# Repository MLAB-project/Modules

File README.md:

# MLAB hardware modules main repository

The MLAB Project was created to develop an universal kit to support hobbyist and professionals in the construction of simple or more complicated devices and instruments (robots, automation systems, testing kits and so on). It is primarily intended for engineers and scientists and it is in continuous development since 2003.

**This repository is archived because its contents have been split into separate repositories in the [MLAB-modules](https://github.com/mlab-modules/) organization. The development of new [MLAB](https://www.mlab.cz) components is still in progress and development has not been suspended. You can read about the reasons of the repository split on the [Discussions thread](https://github.com/orgs/MLAB-project/discussions/1).**

This repository is only a component of the [complete MLAB system](http://www.mlab.cz/)

## Modules

The principle of [Modular LABoratory](http://www.mlab.cz) is based on decomposition of complex systems into smaller cells or bricks (in MLAB called [modules](http://wiki.mlab.cz/doku.php?id=en:moduly)) such as communication interfaces, operational amplifiers, CPU modules, FPGA programmers and many other. Over years of development, [tenths of modules have been created](https://github.com/mlab-modules) - for easier orientation they are sorted into categories which are the first-level folders of this repository. Many modules are included as [repository submodules](https://git-scm.com/book/en/v2/Git-Tools-Submodules) in this parent repository. 

When creating modules, great emphasis is put on the quality of design and construction. The results can, therefore, meet the standards of even the most demanding users from the community of researchers, experimenters and innovators.

## How to start using MLAB

Further information can be found on [MLAB Wiki](http://wiki.mlab.cz/).

There is also a [Mailing list](https://groups.google.com/forum/#!forum/mlab-users) available for users and developers.

## Compatibility

Thanks to careful design, most of the modules are dimensionally and electrically compatible with many other products. Examples include the Arduino platform, the Merkur construction set, optical tables and DIN switchboard systems.

## Applications

See the [list of designs](http://home.mlab.cz/Server/GenIndex/GenIndex.php?path=%2FDesigns&lang=en) for an illustration of the wide spectrum of possible applications.

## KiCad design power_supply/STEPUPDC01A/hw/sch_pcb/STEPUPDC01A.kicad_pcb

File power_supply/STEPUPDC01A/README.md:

<!--- PrjInfo ---> <!--- Please remove this line after manually editing --->
<!--- 00a56be08b96043df9e37d6aff7b6990 --->
<!--- Created:: --->
<!--- Author:: --->
<!--- AuthorEmail:: --->
<!--- Tags:: --->
<!--- Ust:: --->
<!--- Label --->
<!--- ELabel --->
<!--- Name:STEPUPDC01A: --->
# STEPUPDC01A
<!--- LongName --->
Step-Up DC/DC
<!--- ELongName --->

<!--- Lead --->
Vin 3 V - 11 V, Vout up to 36 V, maximal output power 120mW
<!--- ELead --->

<!--- Description --->
<!--- EDescription --->
<!--- Content --->
<!--- EContent --->

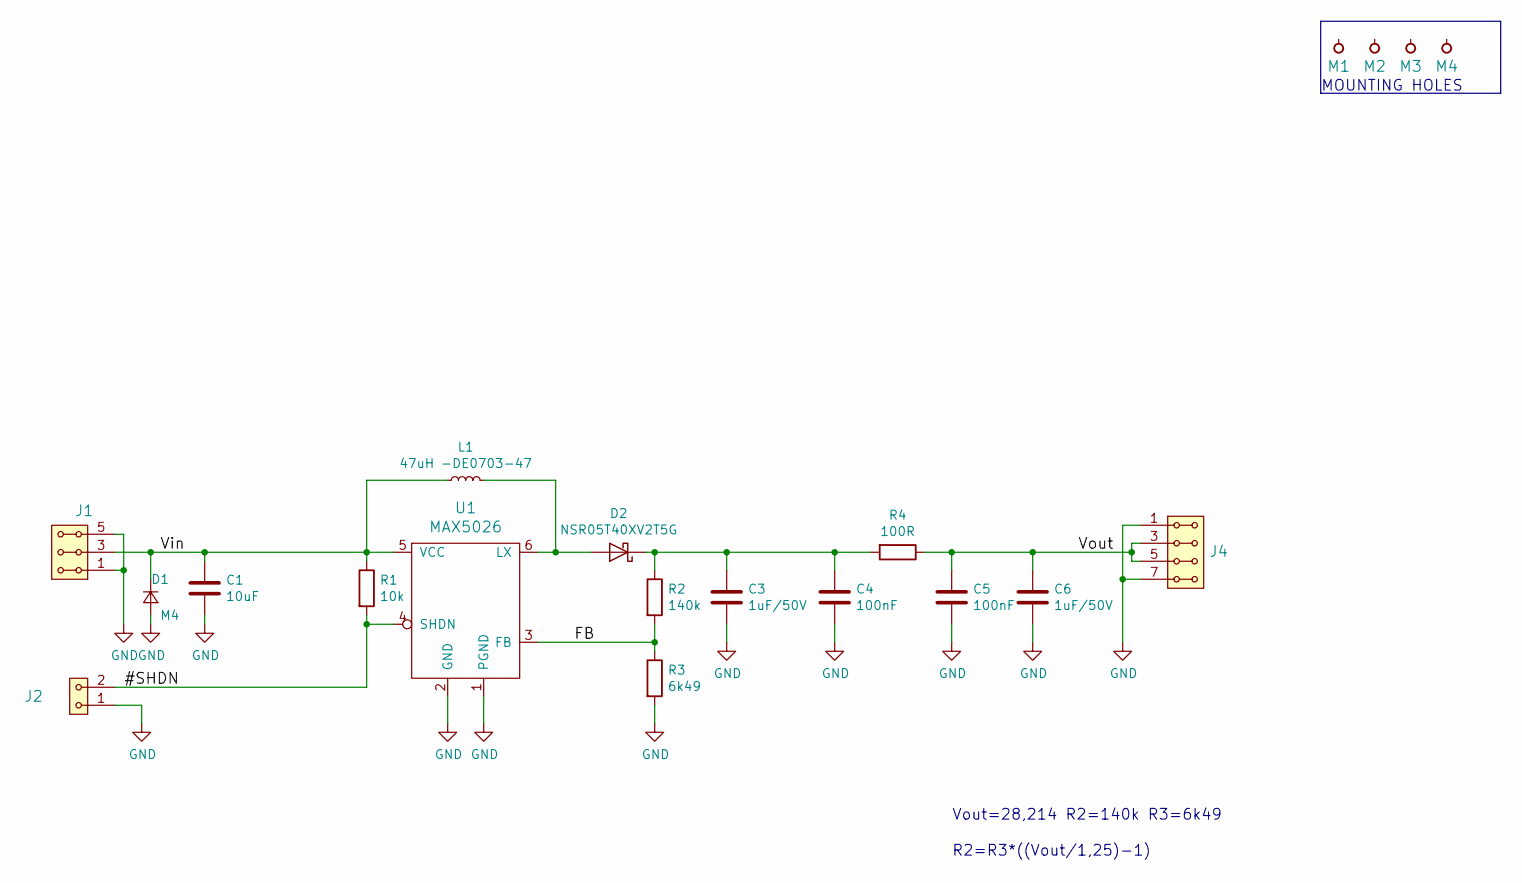
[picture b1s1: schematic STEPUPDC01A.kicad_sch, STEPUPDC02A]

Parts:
C1: 10uF; SMD-0805
C3, C6: 1uF/50V; SMD-0805
C4, C5: 100nF; SMD-0805
D1: M4; Diode-SMA_Standard
D2: NSR05T40XV2T5G; D_SOD-523
J1: HEADER_2x03_PARALLEL; Straight_2x03
J2: HEADER_1x02; Straight_1x02
J4: HEADER_2x04_PARALLEL; Straight_2x04
L1: 47uH -DE0703-47; DE0703
M1, M2, M3, M4: HOLE; MountingHole_3mm
R1: 10k; SMD-0805
R2: 140k; SMD-0805
R3: 6k49; SMD-0805
R4: 100R; SMD-0805
U1: MAX5026; SOT-23-6_Handsoldering

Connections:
/#SHDN: J2.2, R1.2, U1.4 (SHDN)
/FB: R2.2, R3.1, U1.3 (FB)
/Vin: C1.1, D1.1 (K), J1.3, J1.4, L1.1, R1.1, U1.5 (VCC)
/Vout: C5.1, C6.1, J4.3, J4.4, J4.5, J4.6, R4.1
GND: C1.2, C3.2, C4.2, C5.2, C6.2, D1.2 (A), J1.1, J1.2, J1.5, J1.6, J2.1, J4.1, J4.2, J4.7, J4.8, R3.2, U1.1 (PGND), U1.2 (GND)
unnamed: C3.1, C4.1, D2.1 (K), R2.1, R4.2
unnamed: D2.2 (A), L1.2, U1.6 (LX)

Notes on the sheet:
R2=R3*((Vout/1,25)-1)
Vout=28,214 R2=140k R3=6k49
MOUNTING HOLES

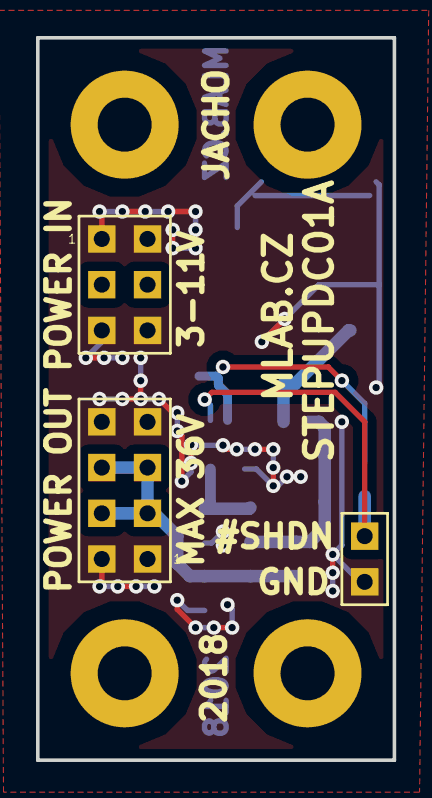
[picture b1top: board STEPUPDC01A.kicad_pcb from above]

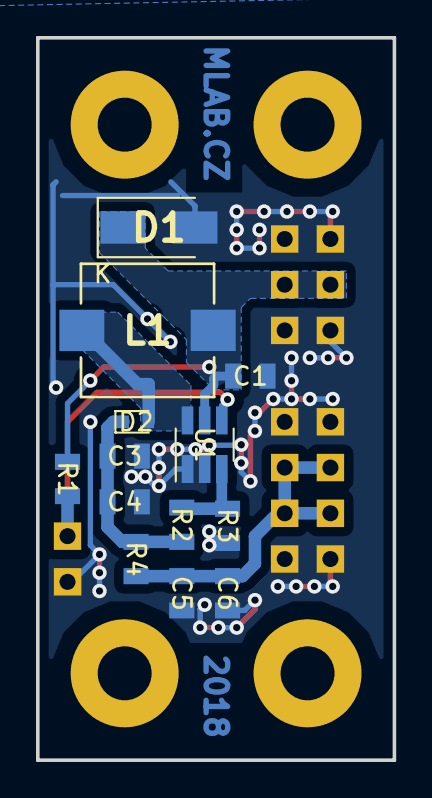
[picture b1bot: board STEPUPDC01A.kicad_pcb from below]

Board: 2 copper layers, 19.8 x 40.1 mm, 20 parts (13 on the bottom side), 7 nets.

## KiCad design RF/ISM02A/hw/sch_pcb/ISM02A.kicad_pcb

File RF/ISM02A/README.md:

<!--- PrjInfo ---> <!--- Please remove this line after manually editing --->
<!--- 00a56be08b96043df9e37d6aff7b6990 --->
<!--- Created:2022-02-16 22:22:32.926193: ---> 
<!--- Author:: ---> 
<!--- AuthorEmail:: ---> 
<!--- Tags:: ---> 
<!--- Ust:: ---> 
<!--- Label --->
<!--- ELabel ---> 
<!--- Name:ISM02A: --->
# ISM02A
<!--- LongName --->
## 
<!--- ELongName ---> 

<!--- Lead --->

<!--- ELead ---> 

<!--- Description --->
<!--- EDescription --->
<!--- Content --->
<!--- EContent --->
<sub><sup> Generated with [MLABweb](https://github.com/MLAB-project/MLABweb). (2022-02-16)</sup></sub>

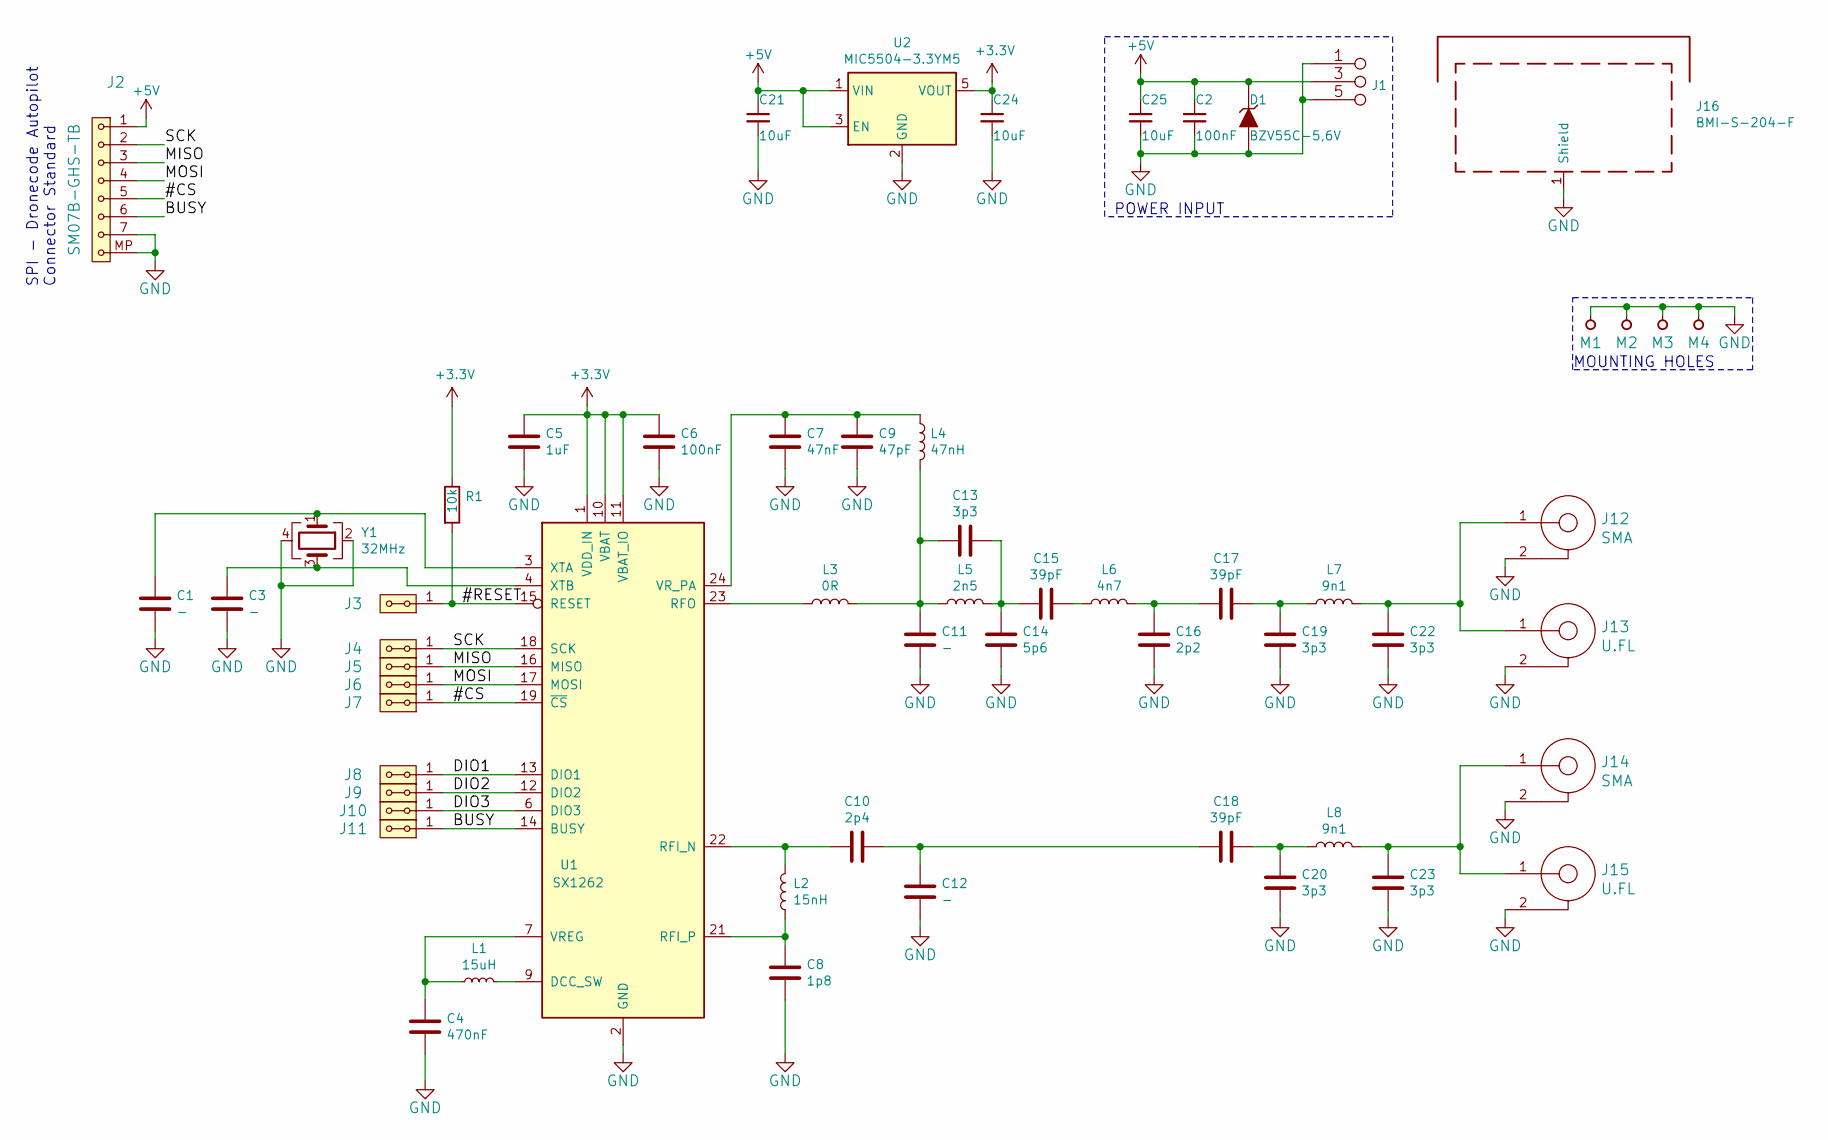
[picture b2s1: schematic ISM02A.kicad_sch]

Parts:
C1, C3, C11, C12: -; C_0603_1608Metric_Pad1.05x0.95mm_HandSolder
C2, C6: 100nF; C_0603_1608Metric_Pad1.05x0.95mm_HandSolder
C4: 470nF; C_0603_1608Metric_Pad1.05x0.95mm_HandSolder
C5: 1uF; C_0603_1608Metric_Pad1.05x0.95mm_HandSolder
C7: 47nF; C_0603_1608Metric_Pad1.05x0.95mm_HandSolder
C8: 1p8; C_0603_1608Metric_Pad1.05x0.95mm_HandSolder
C9: 47pF; C_0603_1608Metric_Pad1.05x0.95mm_HandSolder
C10: 2p4; C_0603_1608Metric_Pad1.05x0.95mm_HandSolder
C13, C19, C20, C22, C23: 3p3; C_0603_1608Metric_Pad1.05x0.95mm_HandSolder
C14: 5p6; C_0603_1608Metric_Pad1.05x0.95mm_HandSolder
C15, C17, C18: 39pF; C_0603_1608Metric_Pad1.05x0.95mm_HandSolder
C16: 2p2; C_0603_1608Metric_Pad1.05x0.95mm_HandSolder
C21, C24, C25: 10uF; SMD-0805
D1: BZV55C-5,6V; Diode-MiniMELF_Standard
J1: JUMP_3X2; Straight_2x03
J2: SM07B-GHS-TB; JST_GH_SM07B-GHS-TB_1x07-1MP_P1.25mm_Horizontal
J3, J4, J5, J6, J7, J8, J9, J10, J11: HEADER_2x01_PARALLEL; Straight_2x01
J12, J14: SMA; SMA6251A13G50
J13, J15: U.FL; U.FL_Hirose_U.FL-R-SMT-1_Vertical
J16: BMI-S-204-F
L1: 15uH; SMD-0805
L2: 15nH; L_0402_1005Metric
L3: 0R; L_0402_1005Metric
L4: 47nH; L_0402_1005Metric
L5: 2n5; L_0402_1005Metric
L6: 4n7; L_0402_1005Metric
L7, L8: 9n1; L_0402_1005Metric
M1, M2, M3, M4: HOLE; MountingHole_3mm
R1: 10k; SMD-0805
U1: SX1262; QFN-24-1EP_4x4mm_P0.5mm_EP2.6x2.6mm_ThermalVias
U2: MIC5504-3.3YM5; SOT-23-5
Y1: 32MHz; Crystal_SMD_NX2016SA

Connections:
+3V3: C5.1, C6.1, C24.1, R1.1, U1.1 (VDD_IN), U1.10 (VBAT), U1.11 (VBAT_IO), U2.5 (VOUT)
+5V: C2.1, C21.1, C25.1, D1.1 (K), J1.3 (4), J1.4, J2.1, U2.1 (VIN), U2.3 (EN)
/#CS: J2.5, J7.1, J7.2, U1.19 (~CS~)
/#RESET: J3.1, J3.2, R1.2, U1.15 (RESET)
/BUSY: J2.6, J11.1, J11.2, U1.14 (BUSY)
/DIO1: J8.1, J8.2, U1.13 (DIO1)
/DIO2: J9.1, J9.2, U1.12 (DIO2)
/DIO3: J10.1, J10.2, U1.6 (DIO3)
/MISO: J2.3, J5.1, J5.2, U1.16 (MISO)
/MOSI: J2.4, J6.1, J6.2, U1.17 (MOSI)
/SCK: J2.2, J4.1, J4.2, U1.18 (SCK)
GND: C1.2, C2.2, C3.2, C4.2, C5.2, C6.2, C7.2, C8.2, C9.2, C11.2, C12.2, C14.2, C16.2, C19.1, C20.1, C21.2, C22.1, C23.1, C24.2, C25.2, D1.2 (A), J1.1 (2), J1.2, J1.5 (6), J1.6, J2.7, J2.MP, J12.2, J13.2, J14.2, J15.2, J16.1, M1.1, M2.1, M3.1, M4.1, U1.2 (GND), U1.5 (GND), U1.8 (GND), U1.20 (GND), U1.25 (GND), U2.2 (GND), Y1.2, Y1.4
unnamed: C1.1, U1.3 (XTA), Y1.1
unnamed: C3.1, U1.4 (XTB), Y1.3
unnamed: C4.1, L1.1, U1.7 (VREG)
unnamed: C7.1, C9.1, L4.1, U1.24 (VR_PA)
unnamed: C8.1, L2.1, U1.21 (RFI_P)
unnamed: C10.1, C12.1, C18.2
unnamed: C10.2, L2.2, U1.22 (RFI_N)
unnamed: C11.1, C13.2, L3.2, L4.2, L5.1
unnamed: C13.1, C14.1, C15.2, L5.2
unnamed: C15.1, L6.1
unnamed: C16.1, C17.2, L6.2
unnamed: C17.1, C19.2, L7.1
unnamed: C18.1, C20.2, L8.1
unnamed: C22.2, J12.1, J13.1, L7.2
unnamed: C23.2, J14.1, J15.1, L8.2
unnamed: L1.2, U1.9 (DCC_SW)
unnamed: L3.1, U1.23 (RFO)

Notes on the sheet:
SPI - Dronecode Autopilot Connector Standard
POWER INPUT
MOUNTING HOLES

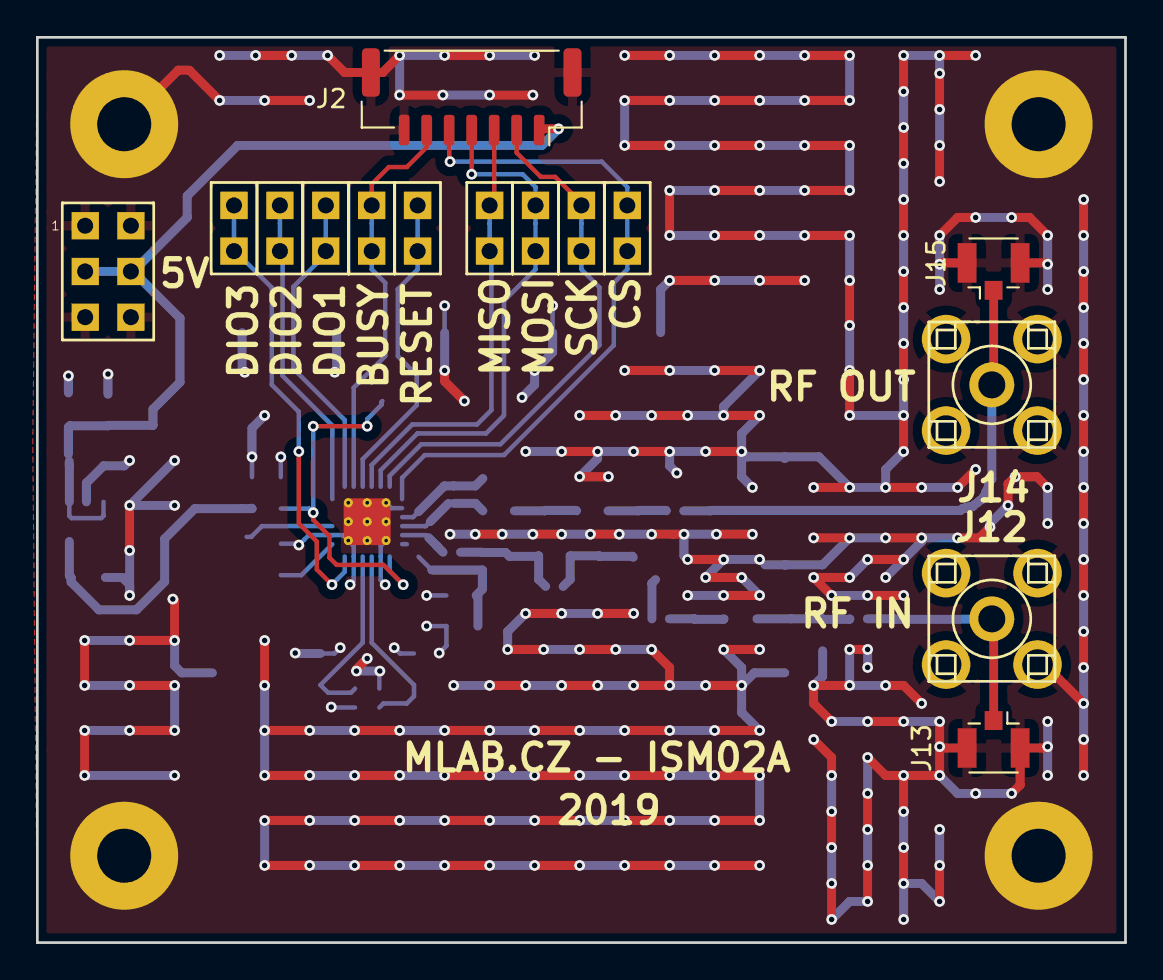
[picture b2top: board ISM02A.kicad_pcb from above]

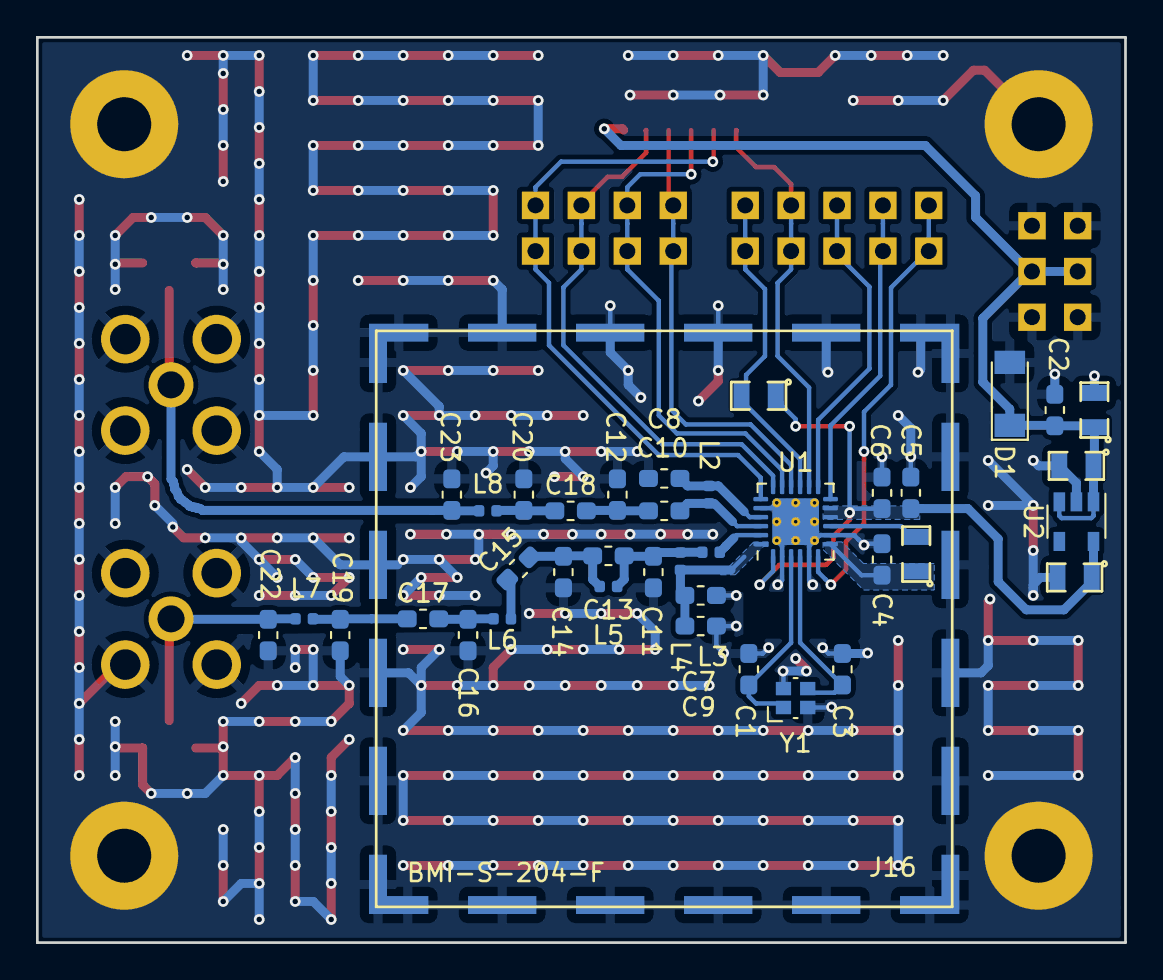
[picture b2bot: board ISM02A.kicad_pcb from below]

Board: 2 copper layers, 60.5 x 50.3 mm, 58 parts (39 on the bottom side), 29 nets.

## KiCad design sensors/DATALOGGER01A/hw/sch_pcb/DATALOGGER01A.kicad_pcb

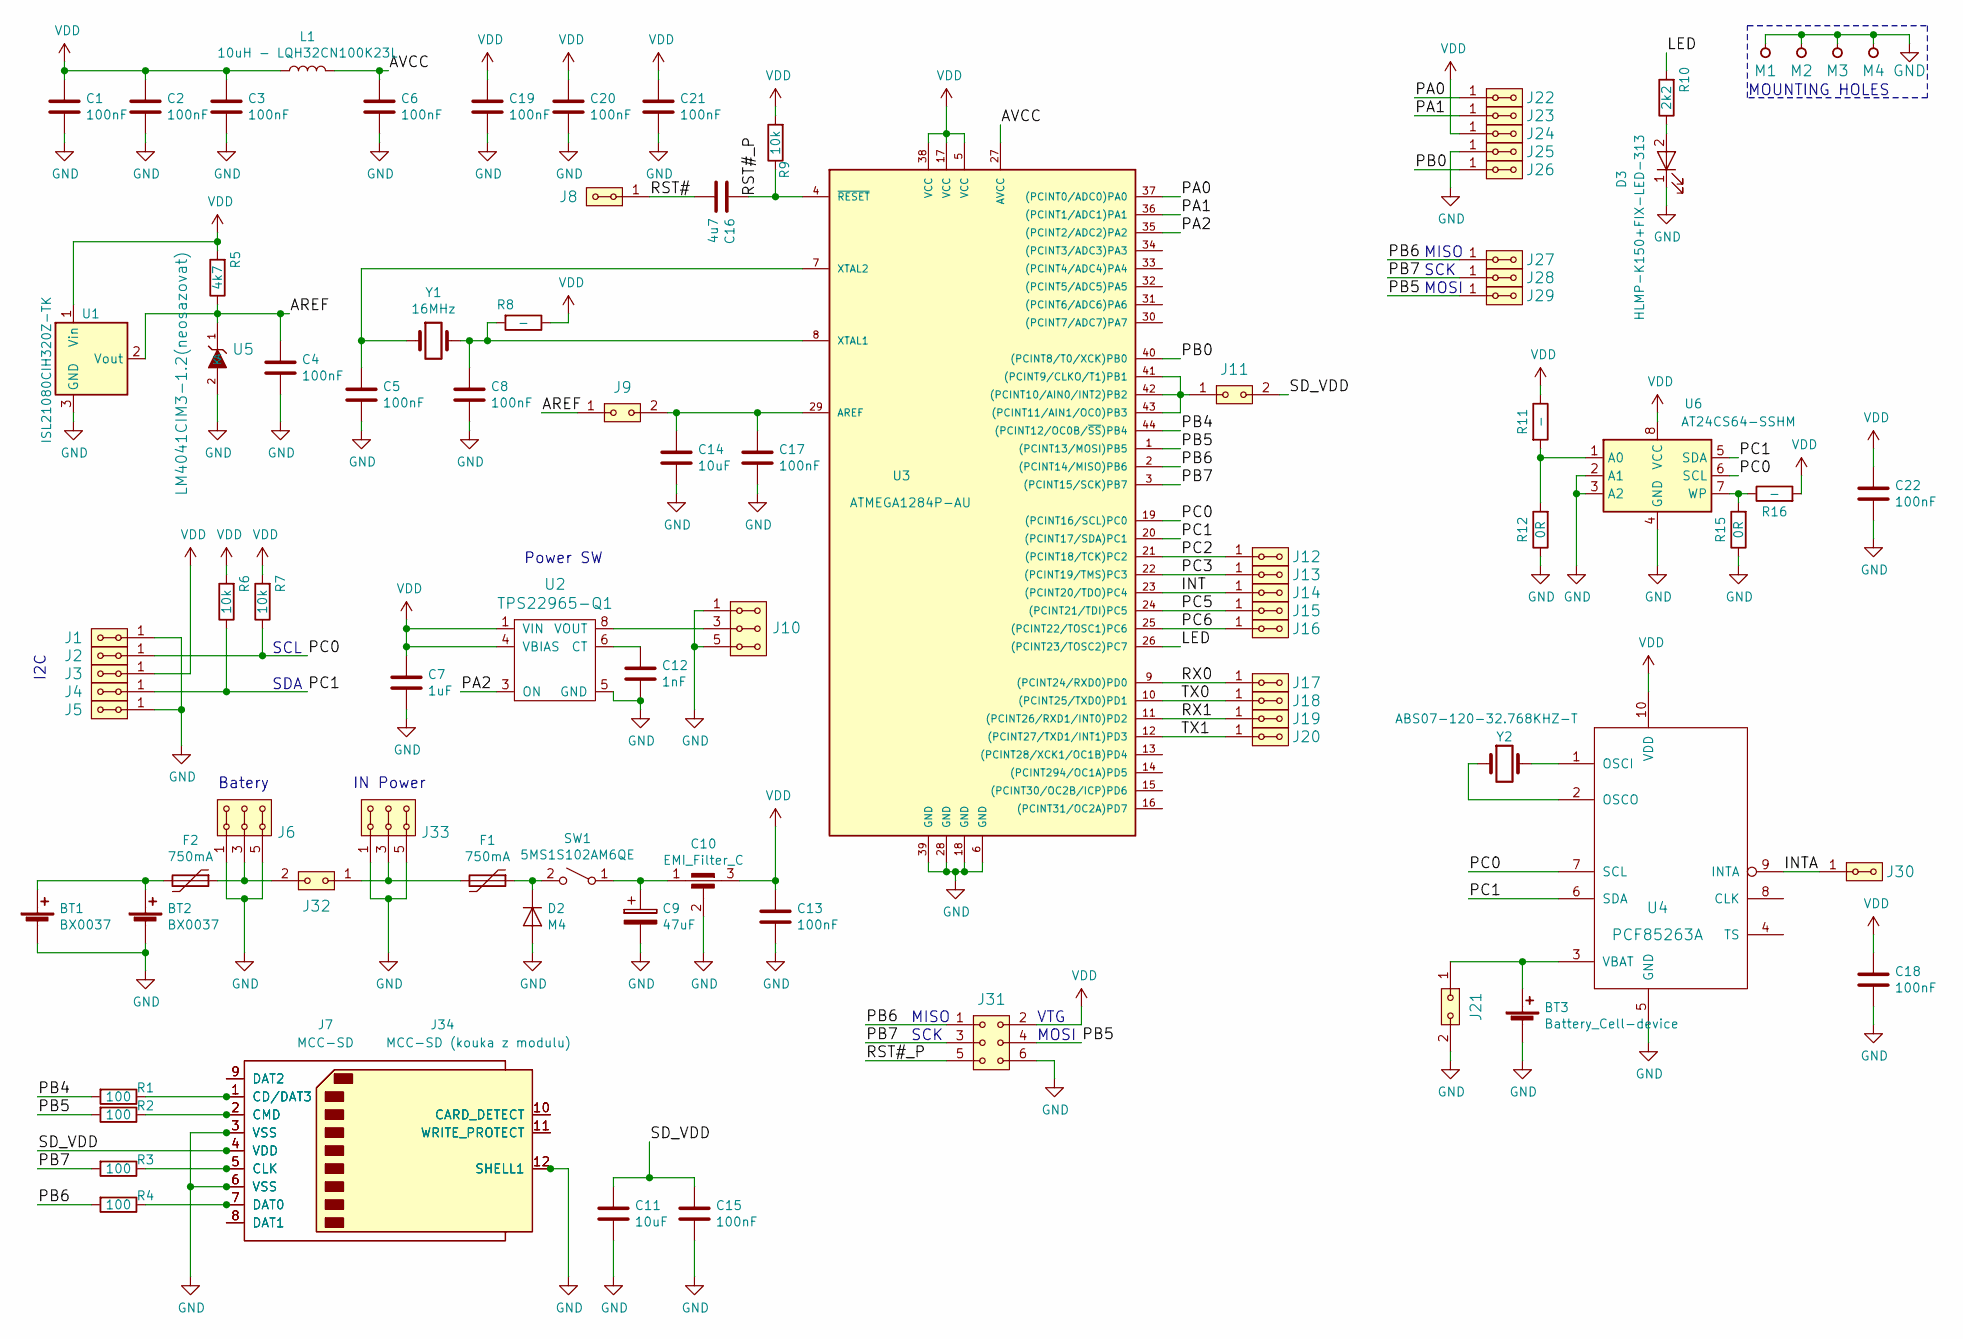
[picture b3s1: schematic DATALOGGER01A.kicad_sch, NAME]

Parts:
BT1, BT2: BX0037
BT3: Battery_Cell-device; CH28-2032
C1, C2, C3, C4, C5, C6, C8, C13, C15, C17, C18, C19, C20, C21, C22: 100nF; SMD-0805
C7: 1uF; SMD-0805
C9: 47uF; TantalC_SizeC_Reflow
C10: EMI_Filter_C; FIR1
C11, C14: 10uF; SMD-0805
C12: 1nF; SMD-0805
C16: 4u7; SMD-0805
D2: M4; SMA_Standard
D3: HLMP-K150+FIX-LED-313; FIX-LED-313
F1, F2: 750mA; 1812
J1, J2, J3, J4, J5, J8, J12, J13, J14, J15, J16, J17, J18, J19, J20, J22, J23, J24, J25, J26, J27, J28, J29, J30: HEADER_2x01_PARALLEL; Straight_2x01
J6, J10, J33: HEADER_2x03_PARALLEL; Straight_2x03
J7: MCC-SD; SD_TE_2041021
J9, J11, J21, J32: HEADER_2x01; Straight_2x01
J31: HEADER_2x03; Straight_2x03
J34: MCC-SD (kouka z modulu); MCC-SD
L1: 10uH - LQH32CN100K23L; SMD-1210
M1, M2, M3, M4: HOLE; MountingHole_3mm
R1, R2, R3, R4: 100; SMD-0805
R5: 4k7; SMD-0805
R6, R7, R9: 10k; SMD-0805
R8, R11, R16: -; SMD-0805
R10: 2k2; SMD-0805
R12, R15: 0R; SMD-0805
SW1: 5MS1S102AM6QE
U1: ISL21080CIH320Z-TK; SOT-23
U2: TPS22965-Q1; WSON-8-1EP_2x2mm_P0.5mm_EP0.9x1.6mm_ThermalVias
U3: ATMEGA1284P-AU; TQFP-44_10x10mm_P0.8mm
U4: PCF85263A; TSSOP-10_3x3mm_Pitch0.5mm
U5: LM4041CIM3-1.2(neosazovat); SOT-23
U6: AT24CS64-SSHM; SOIC-8_3.9x4.9mm_P1.27mm
Y1: 16MHz; Crystal_HC49-U_Vertical
Y2: ABS07-120-32.768KHZ-T; ABS07

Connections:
/AREF: C4.1, J9.1, R5.1, U1.2 (Vout), U5.1 (K)
/AVCC: C6.1, L1.2, U3.27 (AVCC)
/INT: J14.1, J14.2, U3.23 ((PCINT20/TDO)PC4)
/INTA: J30.1, J30.2, U4.9 (INTA)
/LED: R10.2, U3.26 ((PCINT23/TOSC2)PC7)
/PA0: J22.1, J22.2, U3.37 ((PCINT0/ADC0)PA0)
/PA1: J23.1, J23.2, U3.36 ((PCINT1/ADC1)PA1)
/PA2: U2.3 (ON), U3.35 ((PCINT2/ADC2)PA2)
/PB0: J26.1, J26.2, U3.40 ((PCINT8/T0/XCK)PB0)
/PB4: R1.2, U3.44 ((PCINT12/OC0B/~SS~)PB4)
/PB5: J29.1, J29.2, J31.4, R2.2, U3.1 ((PCINT13/MOSI)PB5)
/PB6: J27.1, J27.2, J31.1, R4.2, U3.2 ((PCINT14/MISO)PB6)
/PB7: J28.1, J28.2, J31.3, R3.2, U3.3 ((PCINT15/SCK)PB7)
/PC0: J2.1, J2.2, R7.1, U3.19 ((PCINT16/SCL)PC0), U4.7 (SCL), U6.6 (SCL)
/PC1: J4.1, J4.2, R6.1, U3.20 ((PCINT17/SDA)PC1), U4.6 (SDA), U6.5 (SDA)
/PC2: J12.1, J12.2, U3.21 ((PCINT18/TCK)PC2)
/PC3: J13.1, J13.2, U3.22 ((PCINT19/TMS)PC3)
/PC5: J15.1, J15.2, U3.24 ((PCINT21/TDI)PC5)
/PC6: J16.1, J16.2, U3.25 ((PCINT22/TOSC1)PC6)
/RST#: C16.2, J8.1, J8.2
/RST#_P: C16.1, J31.5, R9.1, U3.4 (~RESET)
/RX0: J17.1, J17.2, U3.9 ((PCINT24/RXD0)PD0)
/RX1: J19.1, J19.2, U3.11 ((PCINT26/RXD1/INT0)PD2)
/SD_VDD: C11.1, C15.1, J7.4 (VDD), J11.2, J34.4 (VDD)
/TX0: J18.1, J18.2, U3.10 ((PCINT25/TXD0)PD1)
/TX1: J20.1, J20.2, U3.12 ((PCINT27/TXD1/INT1)PD3)
GND: BT1.2 (-), BT2.2 (-), BT3.2 (-), C1.2, C2.2, C3.2, C4.2, C5.2, C6.2, C7.2, C8.2, C9.2, C10.2, C11.2, C12.2, C13.2, C14.2, C15.2, C17.2, C18.2, C19.2, C20.2, C21.2, C22.2, D2.2 (A), D3.1 (K), J1.1, J1.2, J5.1, J5.2, J6.1, J6.2, J6.5, J6.6, J7.3 (VSS), J7.6 (VSS), J7.12 (SHELL1), J10.1, J10.2, J10.5, J10.6, J21.2, J25.1, J25.2, J31.6, J33.1, J33.2, J33.5, J33.6, J34.3 (VSS), J34.6 (VSS), J34.12 (SHELL1), M1.1, M2.1, M3.1, M4.1, R12.1, R15.1, U1.3 (GND), U2.5 (GND), U2.9, U3.6 (GND), U3.18 (GND), U3.28 (GND), U3.39 (GND), U4.5 (GND), U5.2 (A), U6.2 (A1), U6.3 (A2), U6.4 (GND)
unnamed: BT1.1 (+), BT2.1 (+), F2.2
unnamed: BT3.1 (+), J21.1, U4.3 (VBAT)
unnamed: C5.1, U3.7 (XTAL2), Y1.1
unnamed: C8.1, R8.2, U3.8 (XTAL1), Y1.2
unnamed: C9.1, C10.1, SW1.1 (A)
unnamed: C12.1, U2.6 (CT)
unnamed: C14.1, C17.1, J9.2, U3.29 (AREF)
unnamed: D2.1 (K), F1.1, SW1.2 (B)
unnamed: D3.2 (A), R10.1
unnamed: F1.2, J32.1, J33.3, J33.4
unnamed: F2.1, J6.3, J6.4, J32.2
unnamed: J10.3, J10.4, U2.7 (VOUT), U2.8 (VOUT)
unnamed: J11.1, U3.41 ((PCINT9/CLKO/T1)PB1), U3.42 ((PCINT10/AIN0/INT2)PB2), U3.43 ((PCINT11/AIN1/OC0)PB3)
unnamed: J7.1 (CD/DAT3), J34.1 (CD/DAT3), R1.1
unnamed: J7.2 (CMD), J34.2 (CMD), R2.1
unnamed: J7.5 (CLK), J34.5 (CLK), R3.1
unnamed: J7.7 (DAT0), J34.7 (DAT0), R4.1
unnamed: J7.8 (DAT1), J34.8 (DAT1)
unnamed: J7.9 (DAT2), J34.9 (DAT2)
unnamed: J7.10 (CARD_DETECT), J34.10 (CARD_DETECT)
unnamed: J7.11 (WRITE_PROTECT), J34.11 (WRITE_PROTECT)
unnamed: R11.2, R12.2, U6.1 (A0)
unnamed: R15.2, R16.1, U6.7 (WP)
unnamed: U4.1 (OSCI), Y2.2
unnamed: U4.2 (OSCO), Y2.1
VDD: C1.1, C2.1, C3.1, C7.1, C10.3, C13.1, C18.1, C19.1, C20.1, C21.1, C22.1, J3.1, J3.2, J24.1, J24.2, J31.2, L1.1, R5.2, R6.2, R7.2, R8.1, R9.2, R11.1, R16.2, U1.1 (Vin), U2.1 (VIN), U2.2 (VIN), U2.4 (VBIAS), U3.5 (VCC), U3.17 (VCC), U3.38 (VCC), U4.10 (VDD), U6.8 (VCC)

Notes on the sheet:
I2C
Batery
SCL
SDA
IN Power
Power SW
MISO
SCK
VTG
MOSI
MOUNTING HOLES

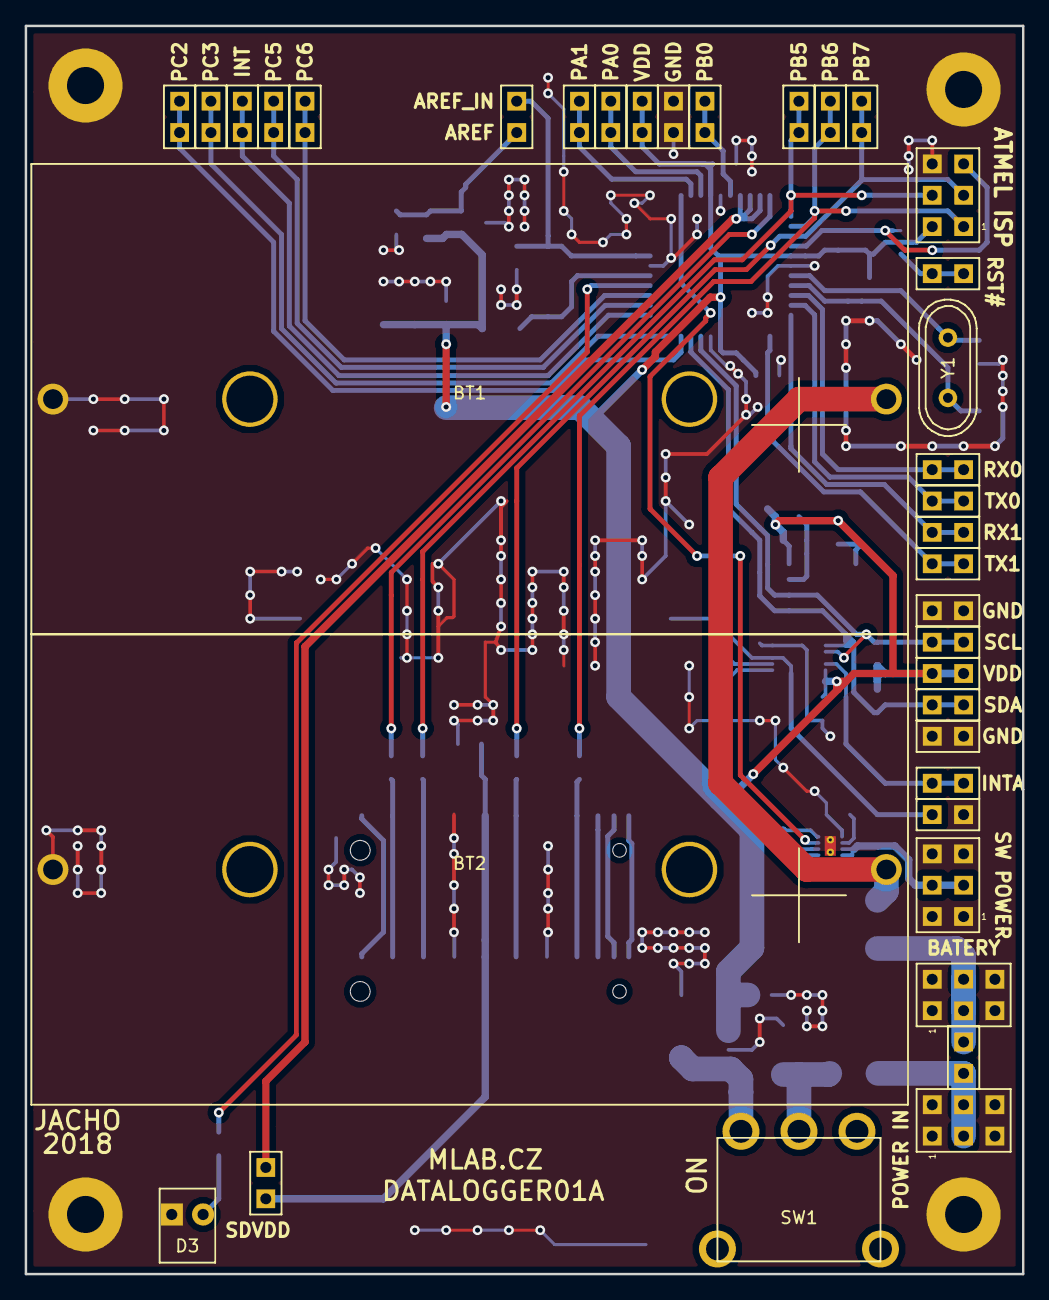
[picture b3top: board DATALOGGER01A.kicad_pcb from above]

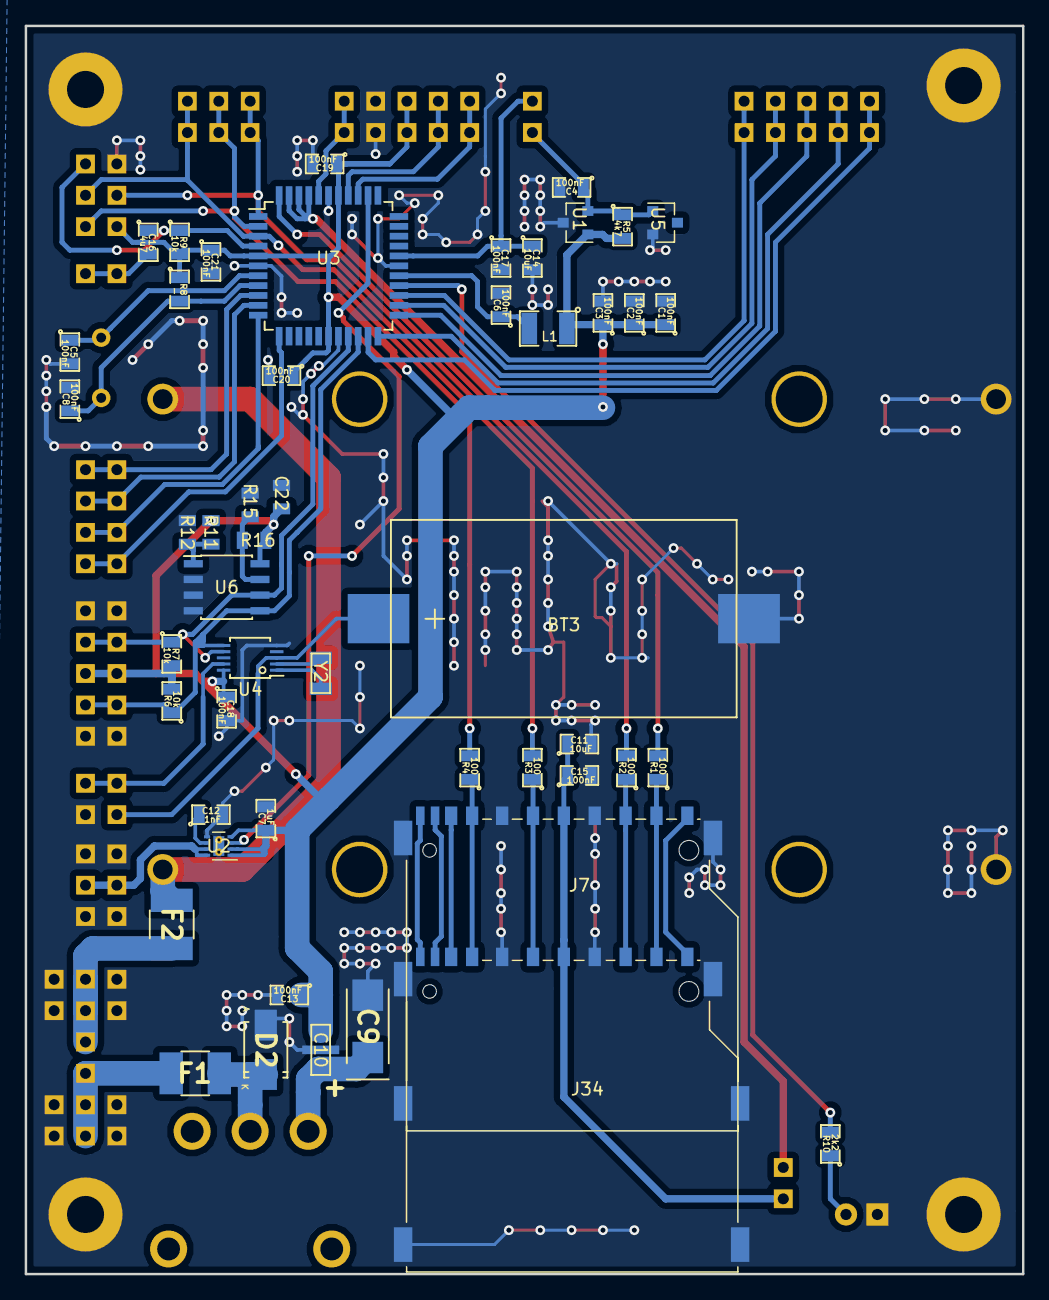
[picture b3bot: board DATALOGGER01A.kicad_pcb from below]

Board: 2 copper layers, 80.8 x 101.1 mm, 91 parts (50 on the bottom side), 53 nets.

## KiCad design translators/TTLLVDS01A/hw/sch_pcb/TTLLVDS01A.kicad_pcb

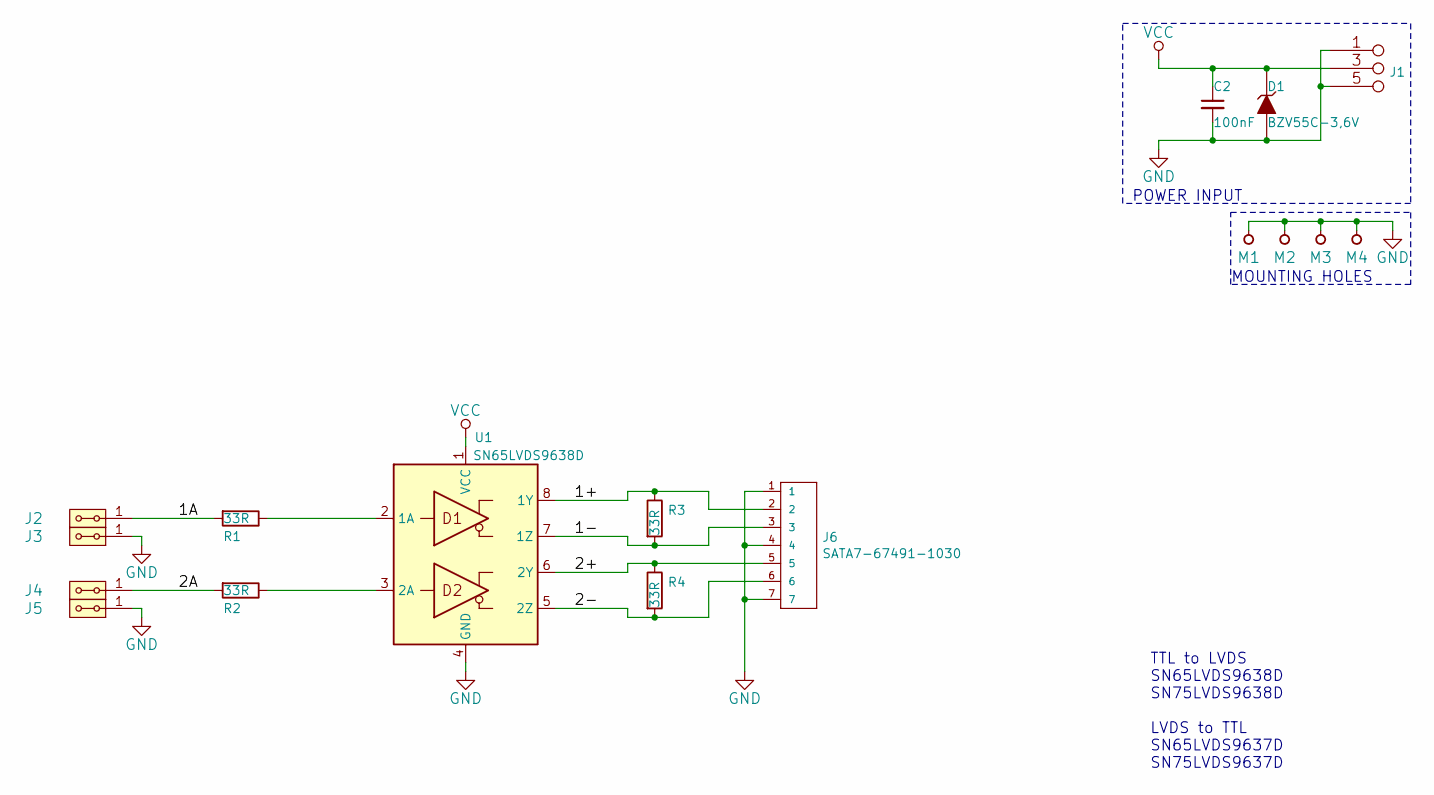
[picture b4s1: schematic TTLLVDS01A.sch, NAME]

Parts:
C2: 100nF; SMD-0805
D1: BZV55C-3,6V; D_MiniMELF
J1: JUMP_3X2; Straight_2x03
J2, J3, J4, J5: HEADER_2x01_PARALLEL; Straight_2x01
J6: SATA7-67491-1030; SATA-7_THT_VERT_2
M1, M2, M3, M4: HOLE; MountingHole_3mm
R1, R2, R3, R4: 33R; SMD-0805
U1: SN65LVDS9638D; SOIC-8_3.9x4.9mm_P1.27mm

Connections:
/1+: J6.2, R3.1, U1.8 (1Y)
/1-: J6.3, R3.2, U1.7 (1Z)
/1A: J2.1, J2.2, R1.2
/2+: J6.5, R4.1, U1.6 (2Y)
/2-: J6.6, R4.2, U1.5 (2Z)
/2A: J4.1, J4.2, R2.2
GND: C2.2, D1.2 (A), J1.1 (2), J1.2, J1.5 (6), J1.6, J3.1, J3.2, J5.1, J5.2, J6.1, J6.4, J6.7, M1.1, M2.1, M3.1, M4.1, U1.4 (GND)
unnamed: R1.1, U1.2 (1A)
unnamed: R2.1, U1.3 (2A)
VCC: C2.1, D1.1 (K), J1.3 (4), J1.4, U1.1 (VCC)

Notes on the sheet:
POWER INPUT
MOUNTING HOLES
TTL to LVDS SN65LVDS9638D SN75LVDS9638D LVDS to TTL SN65LVDS9637D SN75LVDS9637D

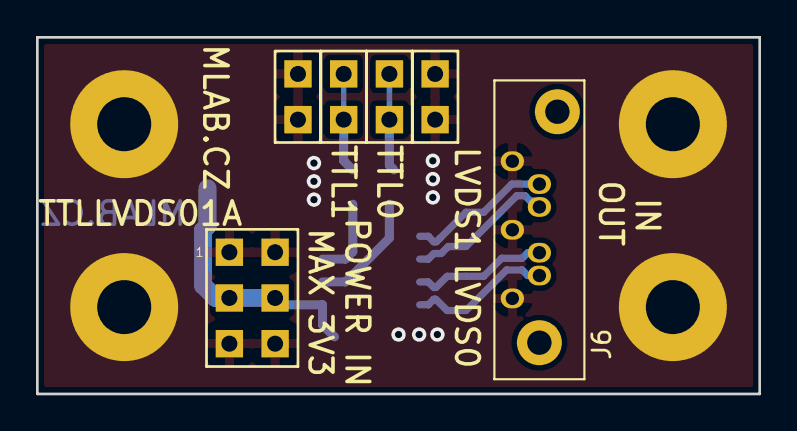
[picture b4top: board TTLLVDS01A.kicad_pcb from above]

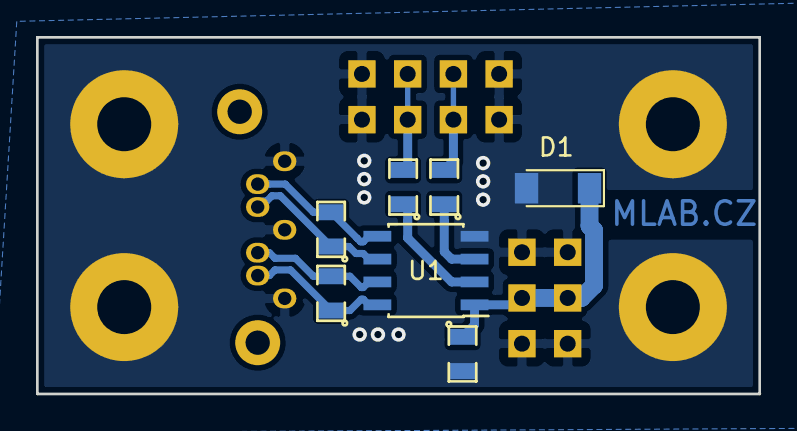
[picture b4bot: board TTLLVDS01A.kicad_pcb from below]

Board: 2 copper layers, 40.1 x 19.8 mm, 17 parts (7 on the bottom side), 10 nets.

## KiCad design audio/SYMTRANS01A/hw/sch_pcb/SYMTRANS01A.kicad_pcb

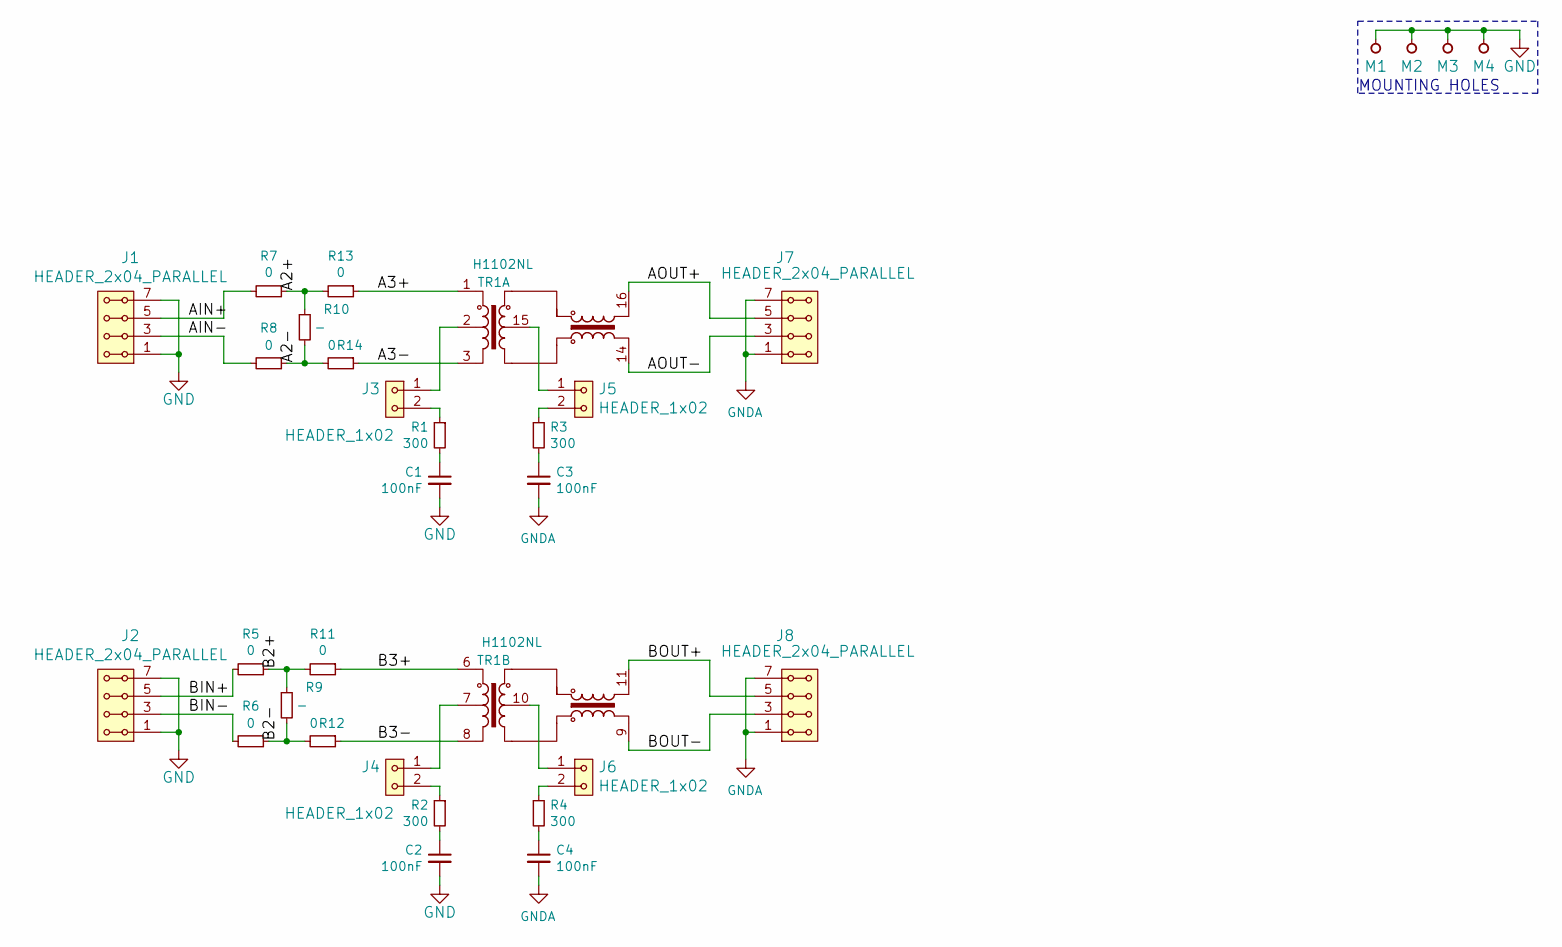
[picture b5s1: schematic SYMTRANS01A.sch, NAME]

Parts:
C1, C2, C3, C4: 100nF; SMD-0805
J1, J2, J7, J8: HEADER_2x04_PARALLEL; Straight_2x04
J3, J4, J5, J6: HEADER_1x02; Straight_2x01
M1, M2, M3, M4: HOLE; MountingHole_3mm
R1, R2, R3, R4: 300; SMD-0805
R5, R6, R7, R8, R11, R12, R13, R14: 0; SMD-0805
R9, R10: -; SMD-0805
TR1: H1102NL; H110X_H1121_HX1188

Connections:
/A2+: R7.1, R10.1, R13.2
/A2-: R8.1, R10.2, R14.2
/A3+: R13.1, TR1.1
/A3-: R14.1, TR1.3
/AIN+: J1.5, J1.6, R7.2
/AIN-: J1.3, J1.4, R8.2
/AOUT+: J7.5, J7.6, TR1.16
/AOUT-: J7.3, J7.4, TR1.14
/B2+: R5.1, R9.1, R11.2
/B2-: R6.1, R9.2, R12.2
/B3+: R11.1, TR1.6
/B3-: R12.1, TR1.8
/BIN+: J2.5, J2.6, R5.2
/BIN-: J2.3, J2.4, R6.2
/BOUT+: J8.5, J8.6, TR1.11
/BOUT-: J8.3, J8.4, TR1.9
GND: C1.2, C2.2, J1.1, J1.2, J1.7, J1.8, J2.1, J2.2, J2.7, J2.8, M1.1, M2.1, M3.1, M4.1
GNDA: C3.2, C4.2, J7.1, J7.2, J7.7, J7.8, J8.1, J8.2, J8.7, J8.8
unnamed: C1.1, R1.2
unnamed: C2.1, R2.2
unnamed: C3.1, R3.2
unnamed: C4.1, R4.2
unnamed: J3.1, TR1.2
unnamed: J3.2, R1.1
unnamed: J4.1, TR1.7
unnamed: J4.2, R2.1
unnamed: J5.1, TR1.15
unnamed: J5.2, R3.1
unnamed: J6.1, TR1.10
unnamed: J6.2, R4.1

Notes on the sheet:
MOUNTING HOLES

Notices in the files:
RF/ISM02A/hw/sch_pcb/ISM02A.kicad_sch:
GPL 3.0
